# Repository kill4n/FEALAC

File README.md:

# FEALAC
FEALAC Open Hardware Proyect
.

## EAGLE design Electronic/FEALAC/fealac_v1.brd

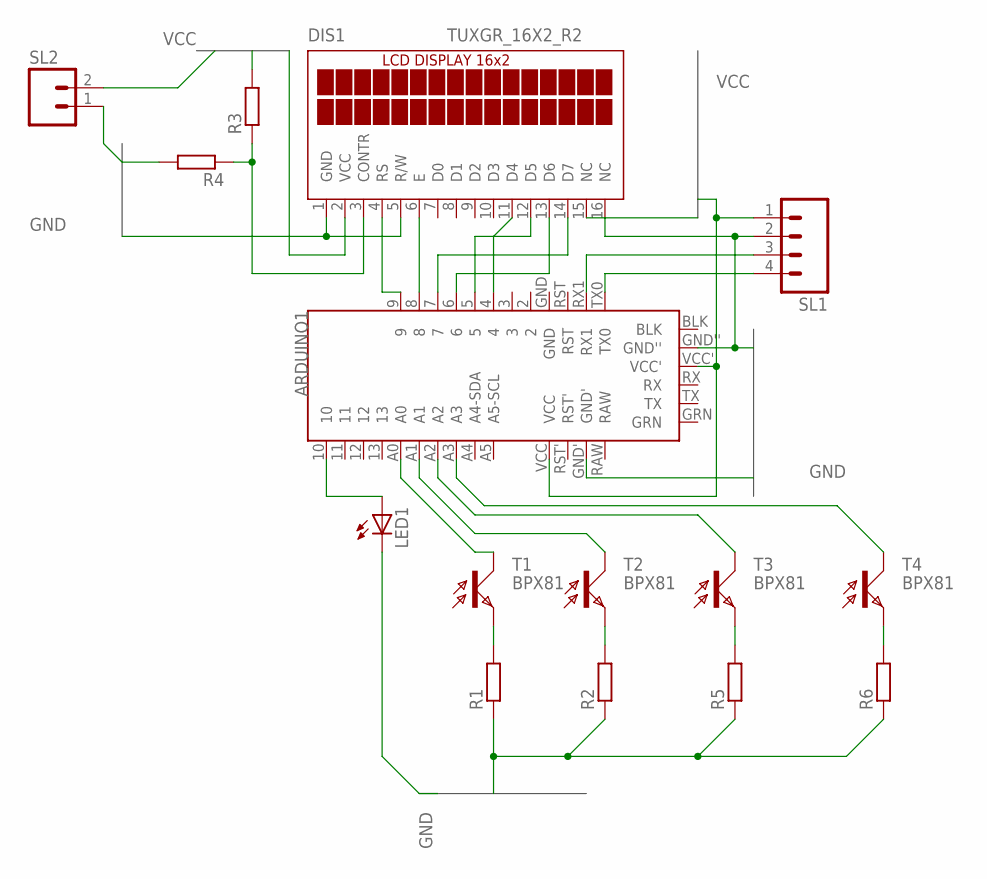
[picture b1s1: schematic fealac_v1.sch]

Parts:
ARDUINO1: ARDUINO_PRO_MINI_V2
DIS1: TUXGR_16X2_R2
LED1: LED3MM
R1, R2, R3, R4, R5, R6: R-EU_0204/7; 0204/7
SL1: M04; 04P
SL2: M02; 02P
T1, T2, T3, T4: BPX81

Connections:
GND: ARDUINO1.GND', ARDUINO1.GND'', DIS1.1 (GND), DIS1.5 (R/W), DIS1.16 (NC), LED1.K (C), R1.1, R2.1, R4.2, R5.1, R6.1, SL1.2, SL2.1
unnamed: DIS1.3 (CONTR), R3.1, R4.1
unnamed: ARDUINO1.4, DIS1.11 (D4)
unnamed: R1.2, T1.E
unnamed: ARDUINO1.RX1, SL1.3
unnamed: ARDUINO1.TX0, SL1.4
unnamed: ARDUINO1.10, LED1.A
unnamed: R6.2, T4.E
unnamed: ARDUINO1.9, DIS1.4 (RS)
unnamed: ARDUINO1.8, DIS1.6 (E)
unnamed: ARDUINO1.7, DIS1.14 (D7)
unnamed: ARDUINO1.6, DIS1.13 (D6)
unnamed: ARDUINO1.5, DIS1.12 (D5)
unnamed: R2.2, T2.E
unnamed: R5.2, T3.E
unnamed: ARDUINO1.A0, T1.C
unnamed: ARDUINO1.A1, T2.C
unnamed: ARDUINO1.A2, T3.C
unnamed: ARDUINO1.A3, T4.C
VCC: ARDUINO1.VCC, ARDUINO1.VCC', DIS1.2 (VCC), DIS1.15 (NC), R3.2, SL1.1, SL2.2

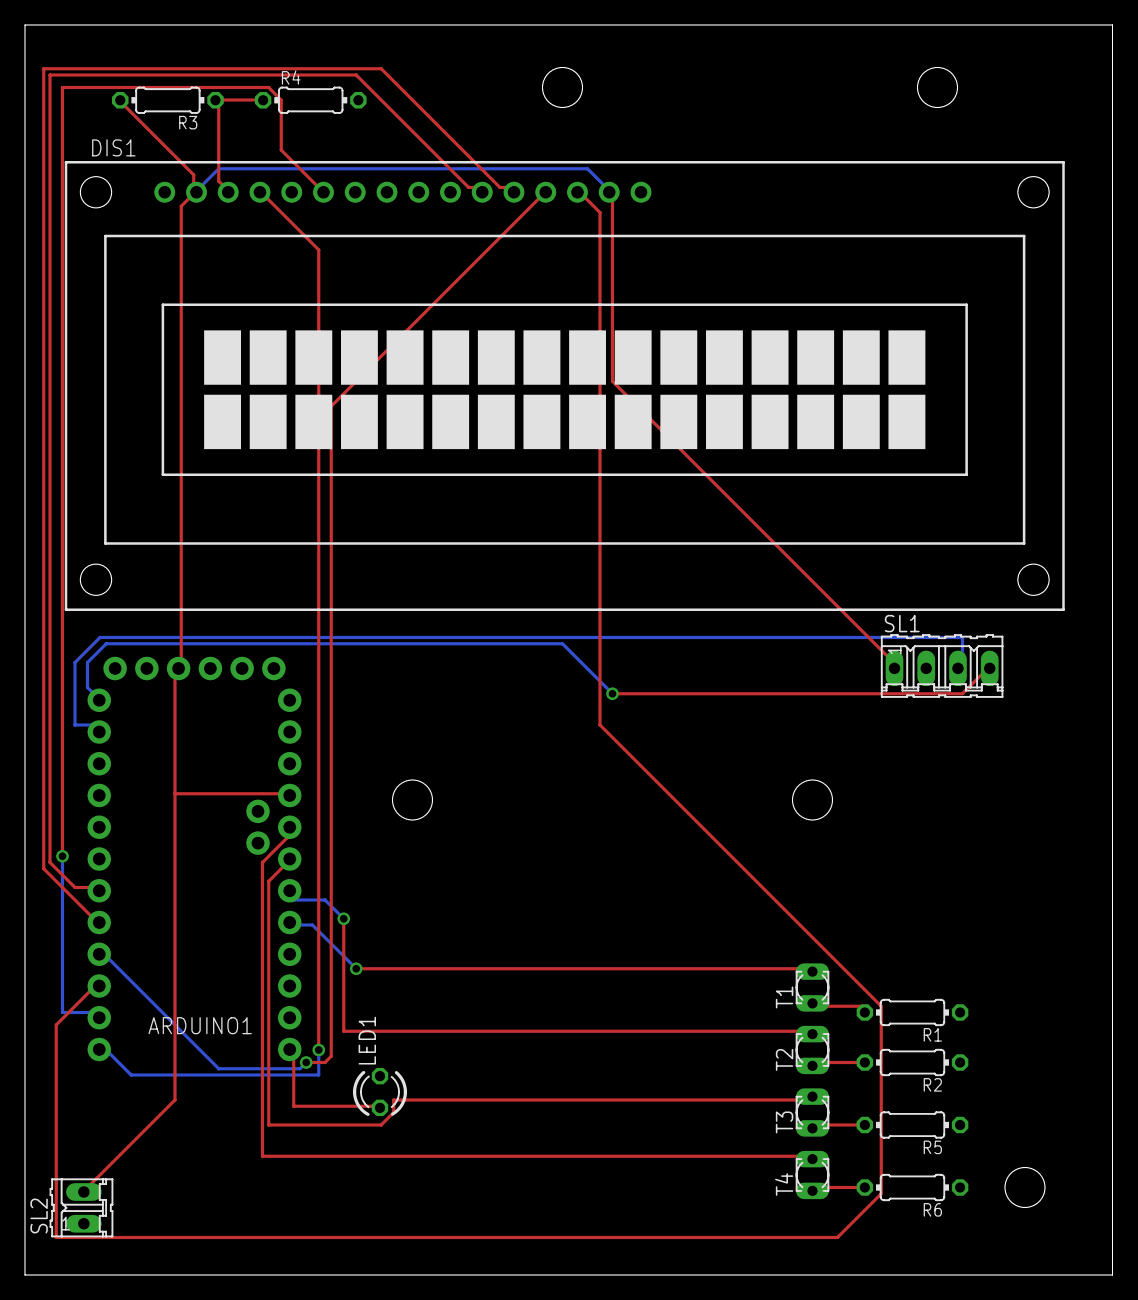
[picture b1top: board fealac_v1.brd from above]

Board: 2 copper layers, 87.0 x 100.0 mm, 15 parts (0 on the bottom side), 20 nets.

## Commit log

2016-03-14 Create gh-pages branch via GitHub
2016-03-14 Hardware
2016-03-14 uploaded
2016-03-14 .
    .
2016-03-14 Documentacion
2016-03-15 changes in idex.md
